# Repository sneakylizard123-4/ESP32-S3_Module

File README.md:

# ESP32-S3 Module

> A Feather-like ESP32-S3 dev board with USB-C, IP5306 battery charging, an onboard NeoPixel, and status LEDs.

This is a small, self-contained development board built around the ESP32-S3-WROOM-1U. The idea is a go-to prototyping board: drop in a LiPo, plug in USB-C, and you have a programmable ESP32-S3 with WiFi/BLE/Zigbee, a NeoPixel for quick visual feedback, and a full set of 2.54mm breakouts. I made it because my other ESP32 boards were either not ESP32-S3, had no USB, or needed an external FTDI adapter just to flash.

**Build status:** assembled and working. USB, charging, the NeoPixel, and the user LED have all been verified on the physical board. See [proof/V1](proof/V1/PROOF.md) for build photos and test results.

## Custom Features

- ESP32-S3-WROOM-1U (N8, 8 MB flash) with WiFi/BLE/Zigbee and a U.FL connector for an external antenna
- IP5306 power path: USB-C charging plus a 5V boost from a single-cell LiPo, with an LED battery gauge
- TLV75733 3.3V LDO for the MCU and logic
- USB-C receptacle with USBLC6-2SC6 ESD protection and 5.1k CC resistors
- Onboard WS2812B NeoPixel and 7 orange status LEDs
- RESET and BOOT buttons, plus an IP5306 power key
- Flashing over the ESP32-S3 native USB or over UART/FTDI through the headers
- 2.54mm header breakouts and a JST-PH battery connector

## How It Works

The board is four functional blocks plus a breakout. USB-C feeds the IP5306, which charges the LiPo and boosts it to a 5V rail. That rail powers the NeoPixel and feeds a TLV75733 LDO, which makes the 3.3V rail for the ESP32-S3. The MCU drives the NeoPixel on GPIO47 and the user LED on GPIO48, and breaks out its remaining IO on the two headers.

| Block | Key parts | What it does |
|-------|-----------|--------------|
| USB input | J1, U1, R1, R2 | USB-C receptacle, ESD protection, and 5.1k CC resistors |
| Charging / boost | U2 (IP5306), L1, R7, C4, C6 | Charges the LiPo and boosts it to +5V, with a LED gauge |
| 3.3V supply | U3 (TLV75733), C3, C5, C7, C10 | LDO that turns +5V into +3.3V for the MCU and logic |
| MCU | U4 (ESP32-S3-WROOM-1U) | WiFi/BLE/Zigbee, native USB, U.FL antenna |
| Indicators | D1-D8, R6, R10, R11 | Power, charge gauge, power key, user LED, NeoPixel |
| Controls | SW1, SW2, SW3 | IP5306 power key, BOOT0, RESET |
| Breakout | J3, J4, J2 | 1x22 and 1x21 headers and a battery connector |

### Power Tree

```mermaid
flowchart LR
  USB["USB-C VBUS"] --> IP5306["IP5306 (U2)"]
  BATT["LiPo JST-PH (J2)"] <--> IP5306
  IP5306 -->|+5V| NEO["WS2812B NeoPixel (D8)"]
  IP5306 -->|+5V| LDO["TLV75733 LDO (U3)"]
  LDO -->|+3.3V| ESP["ESP32-S3-WROOM-1U (U4)"]
  ESP -->|GPIO47| NEO
  ESP -->|GPIO48| LED["User LED (D7)"]
```

## PCB Design

The board is a 4-layer PCB measuring 35.70 x 79.00 mm, with 1.6mm thickness and a dedicated ground inner layer. Power traces are widened and the edges are rounded for handling. Routing is done by hand in KiCad.

Schematic and PCB sources live in [kicad/](kicad/). Fabrication outputs (Gerbers, drill, BOM, pick-and-place) are in [kicad/production/](kicad/production/), and the STEP model is in [cad/](cad/).

## Build

The board was assembled by hand: parts laid out and checked, the USB-C and power sections soldered first, then the headers and the JST-PH battery connector. After that came the power-on checks over USB-C and a power bank.

| | |
|---|---|
|  |  |
|  |  |

The NeoPixel and status LEDs running the self-test: [video/neopixel.mp4](proof/V1/video/neopixel.mp4).

More build and test detail: [proof/V1/PROOF.md](proof/V1/PROOF.md).

## Firmware

The firmware in [firmware/](firmware/) is an interactive self-test over USB CDC. It reports system info and power status, drives the NeoPixel and user LED, reads the BOOT button, runs a GPIO loopback check, and scans for WiFi and BLE networks. It is a PlatformIO project using the Arduino framework, the Adafruit NeoPixel library, and NimBLE-Arduino.

```bash
cd firmware
pio run                 # build
pio run --target upload # flash over USB
```

To enter the bootloader manually:
1. Hold BOOT (SW2 / IO0)
2. Tap RESET (SW3 / EN)
3. Release BOOT
4. Start the upload

See [firmware/README.md](firmware/README.md) for the pin map and library details.

## Usage

### Power

- Charging: plug a USB-C cable into J1. The IP5306 charges the LiPo through J2 and lights the charge gauge.
- Battery: connect a single-cell LiPo to the JST-PH connector (J2).
- The IP5306 power key (SW1) turns the 5V/3.3V rails on and off.

### Programming

- Native USB: connect USB-C and flash the ESP32-S3 directly (GPIO19/GPIO20).
- UART/FTDI: use TXD0 (J4 pin 18) and RXD0 (J4 pin 17) with GND, then trigger BOOT/RESET.

### Pinout

J3 - 1x22 header:

| Pin | Net | Pin | Net |
|-----|-----|-----|-----|
| 1 | GND | 12 | IO8 |
| 2 | +3.3V | 13 | USB_D- |
| 3 | EN | 14 | USB_D+ |
| 4 | IO4 | 15 | IO3 |
| 5 | IO5 | 16 | IO46 |
| 6 | IO6 | 17 | IO9 |
| 7 | IO7 | 18 | IO10 |
| 8 | IO15 | 19 | IO11 |
| 9 | IO16 | 20 | IO12 |
| 10 | IO17 | 21 | +5V |
| 11 | IO18 | 22 | VBUS |

J4 - 1x21 header:

| Pin | Net | Pin | Net |
|-----|-----|-----|-----|
| 1 | +BATT | 12 | IO38 |
| 2 | IO13 | 13 | IO39 |
| 3 | IO14 | 14 | IO40 |
| 4 | IO21 | 15 | IO41 |
| 5 | IO47 (NeoPixel) | 16 | IO42 |
| 6 | IO48 (User LED) | 17 | RXD0 |
| 7 | IO45 | 18 | TXD0 |
| 8 | IO0 (BOOT) | 19 | IO2 |
| 9 | IO35 | 20 | IO1 |
| 10 | IO36 | 21 | GND |
| 11 | IO37 | | |

Note: IO0, IO3, IO45, IO46 are ESP32-S3 strapping pins. Pull them the wrong way at boot and the chip enters a different mode.

## BOM

| Ref | Value | Qty | Unit $ | Ext $ |
|-----|-------|-----|--------|-------|
| C1, C2, C4, C6, C9, C11, C15, C17 | 10uF 25V X5R 0805 | 8 | 0.0871 | 0.6968 |
| C8, C10, C12, C13, C14, C16 | 100nF 50V X7R 0805 | 6 | 0.0266 | 0.1596 |
| C3, C5, C7 | 22uF 25V X5R 0805 | 3 | 0.0698 | 0.2094 |
| D1-D7 | Orange LED 0805 | 7 | 0.0096 | 0.0672 |
| D8 | WS2812B NeoPixel | 1 | 0.0940 | 0.0940 |
| J1 | USB-C receptacle 16P | 1 | 0.1724 | 0.1724 |
| J2 | JST-PH 2P 2mm | 1 | 0.0356 | 0.0356 |
| J3 | Pin header 1x22 2.54mm | 1 | 0.1200 | 0.1200 |
| J4 | Pin header 1x21 2.54mm | 1 | 0.1000 | 0.1000 |
| L1 | 1uH shielded inductor | 1 | 2.5134 | 2.5134 |
| R1, R2 | 5.1k 1% 0805 | 2 | 0.0065 | 0.0130 |
| R3, R5, R6, R8, R9, R10 | 10k 1% 0805 | 6 | 0.0035 | 0.0210 |
| R11 | 330 1% 0805 | 1 | 0.0050 | 0.0050 |
| R4, R7 | 2R 1% 0805 | 2 | 0.0261 | 0.0522 |
| SW1 | Tactile switch EVQPUD | 1 | 0.2299 | 0.2299 |
| SW2, SW3 | Tactile switch KMR2 | 2 | 0.6515 | 1.3030 |
| U1 | USBLC6-2SC6 | 1 | 0.0896 | 0.0896 |
| U2 | IP5306 | 1 | 0.2989 | 0.2989 |
| U3 | TLV75733PDBV | 1 | 0.1819 | 0.1819 |
| U4 | ESP32-S3-WROOM-1U (N8) | 1 | 3.1300 | 3.1300 |
| PCB | Bare PCB (4-layer) | 1 | 1.5000 | 1.5000 |
| **Total** | | **49** | | **10.9929** |

Full BOM with LCSC part numbers, manufacturers, and supplier links: [BOM.csv](BOM.csv). KiCad-generated BOM and pick-and-place: [kicad/production/bom.csv](kicad/production/bom.csv), [kicad/production/positions.csv](kicad/production/positions.csv).

## Production

The board is designed for JLCPCB's standard 4-layer process:

- 4 layers, 1.6mm thick
- HASL lead-free finish
- Gerbers and drill files: [kicad/production/ESP32-S3_Module.zip](kicad/production/ESP32-S3_Module.zip)

## Repository Structure

```
.
|-- BOM.csv                 # Full bill of materials with supplier links
|-- README.md
|-- JOURNAL.md              # Build journal
|-- TIMELINE.md
|-- TODO.md                 # Ideas for v2
|-- cad/                    # STEP model
|-- firmware/               # PlatformIO firmware (Arduino)
|-- images/                 # Schematic, PCB, and render images
|-- kicad/                  # KiCad sources and production outputs
|-- proof/                  # Build and test proof
|-- LICENSE                 # CERN-OHL-P-2.0 (hardware)
`-- LICENSE-MIT             # MIT (firmware)
```

## Known Issues

- WiFi, Bluetooth, and Zigbee have not been exercised yet. The self-test includes WiFi and BLE scan menus, but the radio results have not been confirmed on this board.
- The module uses a U.FL connector instead of an onboard antenna, so an external 2.4 GHz antenna is required for radio range.
- The current layout has DRC issues that should be cleaned up in v2: 2 shorting-item errors and 6 clearance errors around the ESP32 module footprint, plus 3 library footprint mismatch warnings. These are flagged in the committed PCB and did not stop the board from working, but they are not intentional.
- USB-C CC lines are 5.1k sink resistors, so the board draws power but does not negotiate anything above the default USB current.

## Credits & Inspiration

- Form factor inspired by the Adafruit Feather line.
- The IP5306 power section was adapted from my own earlier IP5306-based projects.
- Built with [KiCad](https://www.kicad.org/) and [PlatformIO](https://platformio.org/).
- Firmware uses the [Adafruit NeoPixel](https://github.com/adafruit/Adafruit_NeoPixel) library.
- Espressif ESP32-S3 datasheets and the ESP32-S3 Hardware Design Guidelines.

## License

- Hardware (schematics, PCB, and CAD): CERN Open Hardware Licence Version 2 - Permissive. SPDX: `CERN-OHL-P-2.0`. See [LICENSE](LICENSE).
- Firmware (`firmware/`): MIT License. SPDX: `MIT`. See [LICENSE-MIT](LICENSE-MIT).

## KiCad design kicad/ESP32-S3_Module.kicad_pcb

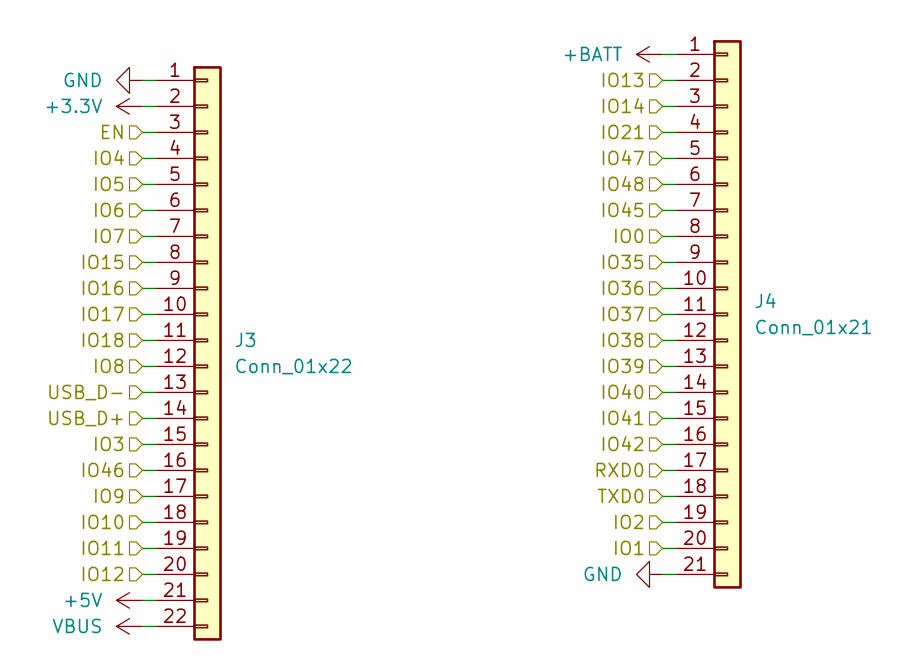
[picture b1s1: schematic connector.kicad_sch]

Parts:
J3: Conn_01x22; PinHeader_1x22_P2.54mm_Vertical
J4: Conn_01x21; PinHeader_1x21_P2.54mm_Vertical

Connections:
+3.3V: J3.2; also elsewhere on the board
+5V: J3.21; also elsewhere on the board
+BATT: J4.1; also elsewhere on the board
/Connector/EN: J3.3; also elsewhere on the board
/Connector/IO0: J4.8; also elsewhere on the board
/Connector/IO1: J4.20; also elsewhere on the board
/Connector/IO2: J4.19; also elsewhere on the board
/Connector/IO3: J3.15; also elsewhere on the board
/Connector/IO4: J3.4; also elsewhere on the board
/Connector/IO5: J3.5; also elsewhere on the board
/Connector/IO6: J3.6; also elsewhere on the board
/Connector/IO7: J3.7; also elsewhere on the board
/Connector/IO8: J3.12; also elsewhere on the board
/Connector/IO9: J3.17; also elsewhere on the board
/Connector/IO10: J3.18; also elsewhere on the board
/Connector/IO11: J3.19; also elsewhere on the board
/Connector/IO12: J3.20; also elsewhere on the board
/Connector/IO13: J4.2; also elsewhere on the board
/Connector/IO14: J4.3; also elsewhere on the board
/Connector/IO15: J3.8; also elsewhere on the board
/Connector/IO16: J3.9; also elsewhere on the board
/Connector/IO17: J3.10; also elsewhere on the board
/Connector/IO18: J3.11; also elsewhere on the board
/Connector/IO21: J4.4; also elsewhere on the board
/Connector/IO35: J4.9; also elsewhere on the board
/Connector/IO36: J4.10; also elsewhere on the board
/Connector/IO37: J4.11; also elsewhere on the board
/Connector/IO38: J4.12; also elsewhere on the board
/Connector/IO39: J4.13; also elsewhere on the board
/Connector/IO40: J4.14; also elsewhere on the board
/Connector/IO41: J4.15; also elsewhere on the board
/Connector/IO42: J4.16; also elsewhere on the board
/Connector/IO45: J4.7; also elsewhere on the board
/Connector/IO46: J3.16; also elsewhere on the board
/Connector/IO47: J4.5; also elsewhere on the board
/Connector/IO48: J4.6; also elsewhere on the board
/Connector/RXD0: J4.17; also elsewhere on the board
/Connector/TXD0: J4.18; also elsewhere on the board
/Connector/USB_D+: J3.14; also elsewhere on the board
/Connector/USB_D-: J3.13; also elsewhere on the board
GND: J3.1, J4.21; also elsewhere on the board
VBUS: J3.22; also elsewhere on the board

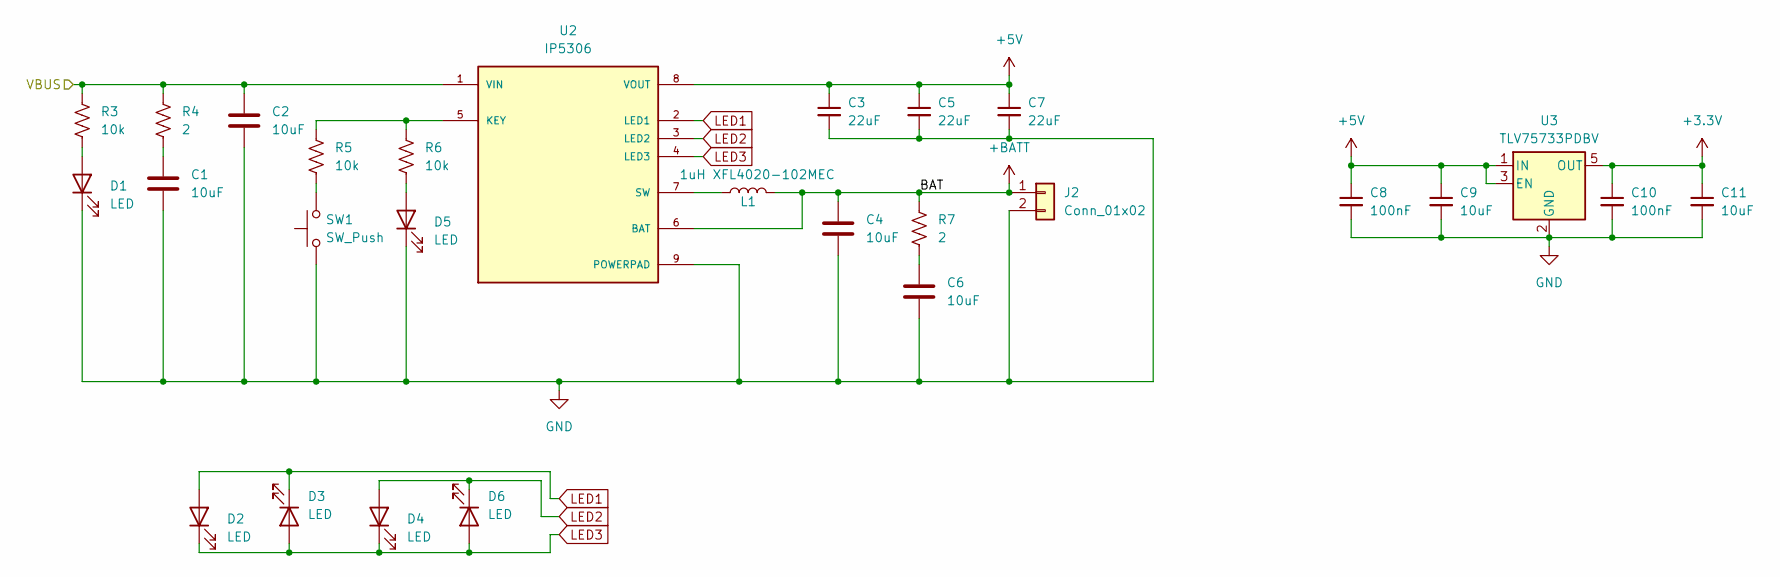
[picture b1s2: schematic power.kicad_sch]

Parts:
C1, C2, C4, C6, C9, C11: 10uF; C_0805_2012Metric
C3, C5, C7: 22uF; C_0805_2012Metric
C8, C10: 100nF; C_0805_2012Metric
D1, D2, D3, D4, D5, D6: LED; LED_0805_2012Metric
J2: Conn_01x02; JST_PH_S2B-PH-SM4-TB_1x02-1MP_P2.00mm_Horizontal
L1: 1uH XFL4020-102MEC; L_Coilcraft_XxL4020
R3, R5, R6: 10k; R_0805_2012Metric
R4, R7: 2; R_0805_2012Metric
SW1: SW_Push; Panasonic_EVQPUM_EVQPUD
U2: IP5306; SOP127P600X165-9N; PARTREV 1.31
U3: TLV75733PDBV; SOT-23-5

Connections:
+3.3V: C10.1, C11.1, U3.5 (OUT); also elsewhere on the board
+5V: C3.1, C5.1, C7.1, C8.1, C9.1, U2.8 (VOUT), U3.1 (IN), U3.3 (EN); also elsewhere on the board
+BATT: C4.1, J2.1, L1.2, R7.1, U2.6 (BAT); also elsewhere on the board
GND: C1.2, C2.2, C3.2, C4.2, C5.2, C6.2, C7.2, C8.2, C9.2, C10.2, C11.2, D1.1 (K), D5.1 (K), J2.2, SW1.1, U2.9 (POWERPAD), U3.2 (GND); also elsewhere on the board
LED1: D2.2 (A), D3.1 (K), U2.2 (LED1)
LED2: D4.2 (A), D6.1 (K), U2.3 (LED2)
LED3: D2.1 (K), D3.2 (A), D4.1 (K), D6.2 (A), U2.4 (LED3)
unnamed: C1.1, R4.2
unnamed: C6.1, R7.2
unnamed: D1.2 (A), R3.2
unnamed: D5.2 (A), R6.2
unnamed: R5.2, SW1.2
unnamed: R5.1, R6.1, U2.5 (KEY)
unnamed: L1.1, U2.7 (SW)
VBUS: C2.1, R3.1, R4.1, U2.1 (VIN); also elsewhere on the board

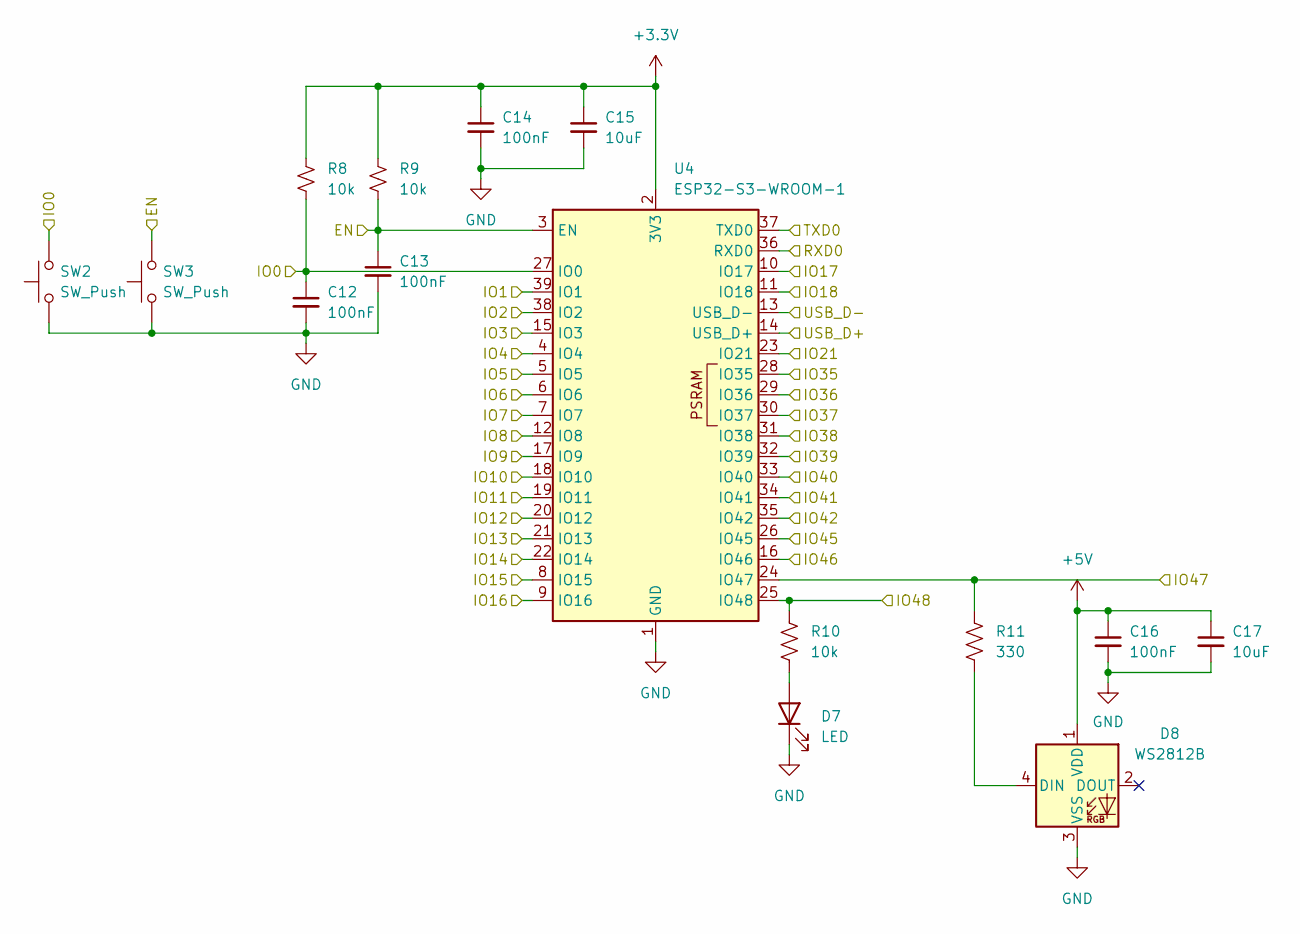
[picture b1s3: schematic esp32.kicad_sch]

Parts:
C12, C13, C14, C16: 100nF; C_0805_2012Metric
C15, C17: 10uF; C_0805_2012Metric
D7: LED; LED_0805_2012Metric
D8: WS2812B; LED_WS2812B-Mini_PLCC4_3.5x3.5mm
R8, R9, R10: 10k; R_0805_2012Metric
R11: 330; R_0805_2012Metric
SW2, SW3: SW_Push; SW_Push_1P1T_NO_CK_KMR2
U4: ESP32-S3-WROOM-1; ESP32-S3-WROOM-1U

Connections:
+3.3V: C14.1, C15.1, R8.1, R9.1, U4.2 (3V3); also elsewhere on the board
+5V: C16.1, C17.1, D8.1 (VDD); also elsewhere on the board
/Connector/EN: C13.1, R9.2, SW3.2, U4.3 (EN); also elsewhere on the board
/Connector/IO0: C12.1, R8.2, SW2.2, U4.27 (IO0); also elsewhere on the board
/Connector/IO1: U4.39 (IO1); also elsewhere on the board
/Connector/IO2: U4.38 (IO2); also elsewhere on the board
/Connector/IO3: U4.15 (IO3); also elsewhere on the board
/Connector/IO4: U4.4 (IO4); also elsewhere on the board
/Connector/IO5: U4.5 (IO5); also elsewhere on the board
/Connector/IO6: U4.6 (IO6); also elsewhere on the board
/Connector/IO7: U4.7 (IO7); also elsewhere on the board
/Connector/IO8: U4.12 (IO8); also elsewhere on the board
/Connector/IO9: U4.17 (IO9); also elsewhere on the board
/Connector/IO10: U4.18 (IO10); also elsewhere on the board
/Connector/IO11: U4.19 (IO11); also elsewhere on the board
/Connector/IO12: U4.20 (IO12); also elsewhere on the board
/Connector/IO13: U4.21 (IO13); also elsewhere on the board
/Connector/IO14: U4.22 (IO14); also elsewhere on the board
/Connector/IO15: U4.8 (IO15); also elsewhere on the board
/Connector/IO16: U4.9 (IO16); also elsewhere on the board
/Connector/IO17: U4.10 (IO17); also elsewhere on the board
/Connector/IO18: U4.11 (IO18); also elsewhere on the board
/Connector/IO21: U4.23 (IO21); also elsewhere on the board
/Connector/IO35: U4.28 (IO35); also elsewhere on the board
/Connector/IO36: U4.29 (IO36); also elsewhere on the board
/Connector/IO37: U4.30 (IO37); also elsewhere on the board
/Connector/IO38: U4.31 (IO38); also elsewhere on the board
/Connector/IO39: U4.32 (IO39); also elsewhere on the board
/Connector/IO40: U4.33 (IO40); also elsewhere on the board
/Connector/IO41: U4.34 (IO41); also elsewhere on the board
/Connector/IO42: U4.35 (IO42); also elsewhere on the board
/Connector/IO45: U4.26 (IO45); also elsewhere on the board
/Connector/IO46: U4.16 (IO46); also elsewhere on the board
/Connector/IO47: R11.1, U4.24 (IO47); also elsewhere on the board
/Connector/IO48: R10.1, U4.25 (IO48); also elsewhere on the board
/Connector/RXD0: U4.36 (RXD0); also elsewhere on the board
/Connector/TXD0: U4.37 (TXD0); also elsewhere on the board
/Connector/USB_D+: U4.14 (USB_D+); also elsewhere on the board
/Connector/USB_D-: U4.13 (USB_D-); also elsewhere on the board
GND: C12.2, C13.2, C14.2, C15.2, C16.2, C17.2, D7.1 (K), D8.3 (VSS), SW2.1, SW3.1, U4.1 (GND), U4.40 (GND), U4.41 (GND); also elsewhere on the board
unnamed: D7.2 (A), R10.2
unnamed: D8.4 (DIN), R11.2

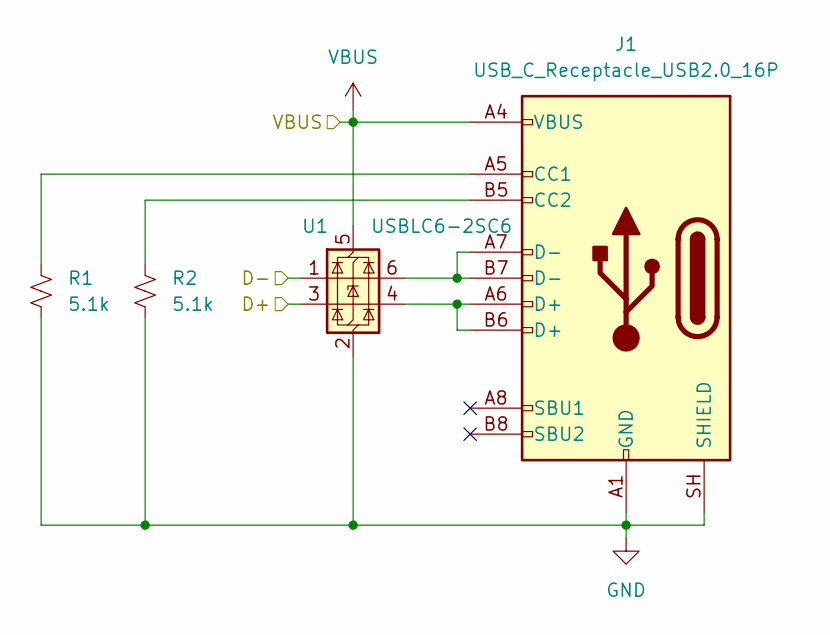
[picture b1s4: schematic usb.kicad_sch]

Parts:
J1: USB_C_Receptacle_USB2.0_16P; USB_C_Receptacle_HRO_TYPE-C-31-M-12
R1, R2: 5.1k; R_0805_2012Metric
U1: USBLC6-2SC6; SOT-23-6

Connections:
/Connector/USB_D+: U1.3 (I/O2); also elsewhere on the board
/Connector/USB_D-: U1.1 (I/O1); also elsewhere on the board
GND: J1.A1 (GND), J1.A12 (GND), J1.B1 (GND), J1.B12 (GND), J1.SH (SHIELD), R1.2, R2.2, U1.2 (GND); also elsewhere on the board
unnamed: J1.A5 (CC1), R1.1
unnamed: J1.B5 (CC2), R2.1
unnamed: J1.A6 (D+), J1.B6 (D+), U1.4 (I/O2)
unnamed: J1.A7 (D-), J1.B7 (D-), U1.6 (I/O1)
VBUS: J1.A4 (VBUS), J1.A9 (VBUS), J1.B4 (VBUS), J1.B9 (VBUS), U1.5 (VBUS); also elsewhere on the board

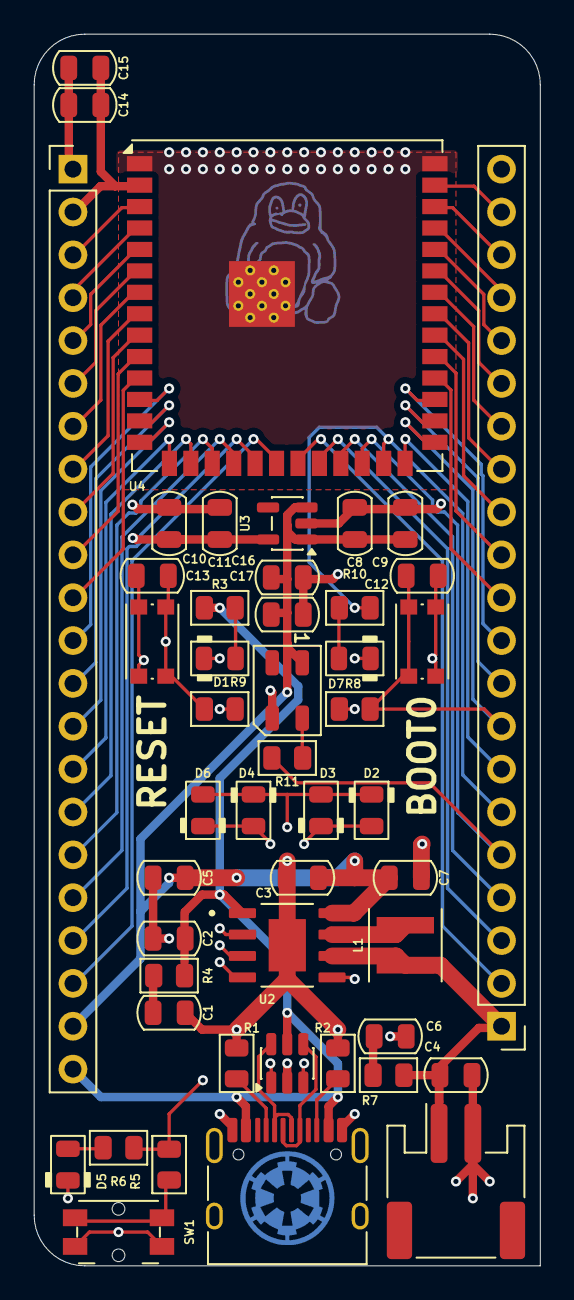
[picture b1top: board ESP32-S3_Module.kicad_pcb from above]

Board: 4 copper layers, 30.0 x 73.0 mm, 48 parts (0 on the bottom side), 58 nets.

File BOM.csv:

Ref,Value,LCSC#,MPN,Manufacturer,Footprint,Qty,Unit Price($),Ext Price($),Supplier Link
"C1, C11, C15, C17, C2, C4, C6, C9",10uF 25V X5R,C15850,CL21A106KAYNNNE,Samsung,0805,8,0.0871,0.6968,https://www.lcsc.com/product-detail/C15850.html
"C10, C12, C13, C14, C16, C8",100nF 50V X7R,C1711,CC0805KRX7R9BB104,YAGEO,0805,6,0.0266,0.1596,https://www.lcsc.com/product-detail/C1711.html
"C3, C5, C7",22uF 25V X5R,C86816,GRM21BR61E226ME44L,muRata,0805,3,0.0698,0.2094,https://www.lcsc.com/product-detail/C86816.html
"D1, D2, D3, D4, D5, D6, D7",Orange LED 0805,C965813,XL-2012UOC,XINGLIGHT,0805,7,0.0096,0.0672,https://www.lcsc.com/product-detail/C965813.html
D8,WS2812B,C2761795,WS2812B-B/T,Worldsemi,PLCC4 5050,1,0.0940,0.0940,https://www.lcsc.com/product-detail/C2761795.html
J1,USB-C Receptacle 16P,C165948,TYPE-C-31-M-12,Korean Hroparts Elec,SMD,1,0.1724,0.1724,https://www.lcsc.com/product-detail/C165948.html
J2,JST PH 2P 2mm,C131337,B2B-PH-K-S(LF)(SN),JST,Through Hole,1,0.0356,0.0356,https://www.lcsc.com/product-detail/C131337.html
J3,Pin Header 1x22 2.54mm,C41375941,HC-PZ254-11.5L-1x22PZ,Hong Cheng,Through Hole,1,0.1200,0.1200,https://www.lcsc.com/product-detail/C41375941.html
J4,Pin Header 1x21 2.54mm,C49569644,2011-1X21G00SB,WingTAT,Through Hole,1,0.1000,0.1000,https://www.lcsc.com/product-detail/C49569644.html
L1,1uH Shielded Inductor,C5355380,XFL4020-102MEC,Coilcraft,SMD 4x4mm,1,2.5134,2.5134,https://www.lcsc.com/product-detail/C5355380.html
"R1, R2",5.1k 1% 0805,C27834,0805W8F5101T5E,UNI-ROYAL,0805,2,0.0065,0.0130,https://www.lcsc.com/product-detail/C27834.html
"R10, R3, R5, R6, R8, R9",10k 1% 0805,C2907219,FRC0805F1002TS,FOJAN,0805,6,0.0035,0.0210,https://www.lcsc.com/product-detail/C2907219.html
R11,330 1% 0805,C2889518,0805 1% 330 OHM,VO,0805,1,0.0050,0.0050,https://www.lcsc.com/product-detail/C2889518.html
"R4, R7",2R 1% 0805,C114246,RC0805FR-072RL,YAGEO,0805,2,0.0261,0.0522,https://www.lcsc.com/product-detail/C114246.html
SW1,Tactile Switch EVQPUD,C388885,EVQPUD02K,PANASONIC,SMD,1,0.2299,0.2299,https://www.lcsc.com/product-detail/C388885.html
"SW2, SW3",Tactile Switch KMR2,C72443,KMR221GLFS,C&K,SMD,2,0.6515,1.3030,https://www.lcsc.com/product-detail/C72443.html
U1,USBLC6-2SC6,C7519,USBLC6-2SC6,ST,SOT-23-6,1,0.0896,0.0896,https://www.lcsc.com/product-detail/C7519.html
U2,IP5306,C181692,IP5306,INJOINIC,ESOP-8,1,0.2989,0.2989,https://www.lcsc.com/product-detail/C181692.html
U3,TLV75733PDBV,C485517,TLV75733PDBVR,TI,SOT-23-5,1,0.1819,0.1819,https://www.lcsc.com/product-detail/C485517.html
U4,ESP32-S3-WROOM-1U,C2913202,ESP32-S3-WROOM-1-N8,ESPRESSIF,SMD WROOM,1,3.1300,3.1300,https://www.lcsc.com/product-detail/C2913202.html
PCB,Bare PCB,,,,,1,1.5000,1.5000,
Total,,,Components (9.4929) + PCB (1.50) = Total,,,,,10.9929,
